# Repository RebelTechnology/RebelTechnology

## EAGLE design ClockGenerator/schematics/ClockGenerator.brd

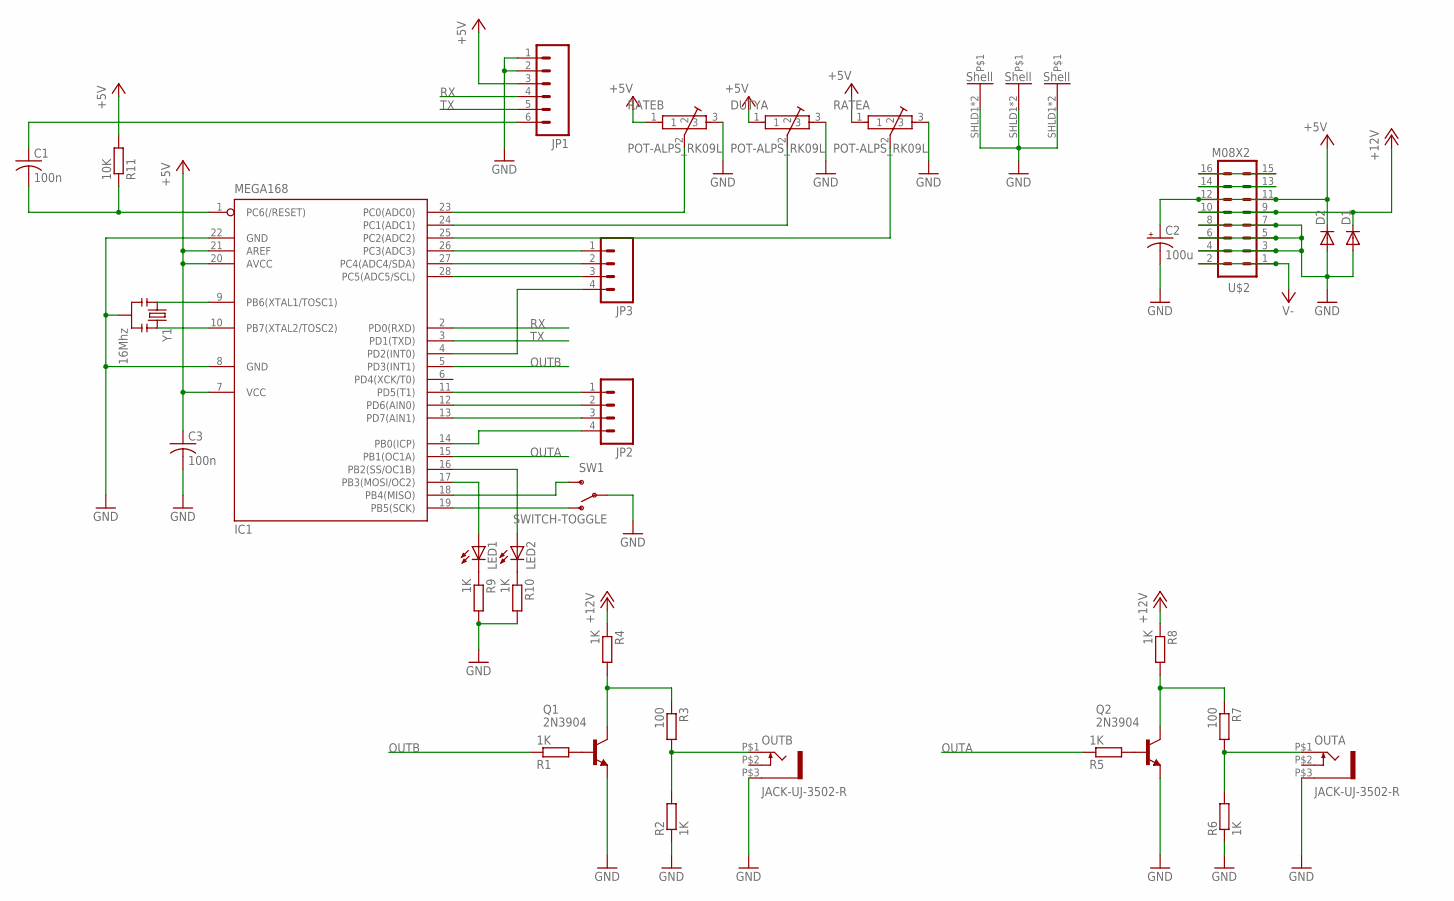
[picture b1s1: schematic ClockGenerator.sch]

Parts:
C1, C3: 100n; C050-024X044
C2: 100u; CPOL-RADIAL-100UF-25V
D1, D2: DIODEPTH; DIODE-1N4001
DUTYA: POT-ALPS_RK09L; POT-ALPS_RK09L1120
IC1: MEGA168; DIL28-3
JP1: M06SIP; 1X06
JP2, JP3: M04PTH; 1X04
LED1, LED2: LED3MM
OUTA: JACK-UJ-3502-R; UJ-3502-R
OUTB: JACK-UJ-3502-R; UJ-3502-R
Q1, Q2: 2N3904; TO92
R1, R2, R4, R5, R6, R8, R9, R10: 1K; 0204/7
R3, R7: 100; 0204/7
R11: 10K; 0204/7
RATEA: POT-ALPS_RK09L; POT-ALPS_RK09L1120
RATEB: POT-ALPS_RK09L; POT-ALPS_RK09L1120
SW1: SWITCH-TOGGLE; SWITCH-SPDT-SALECOM-T8020
U$2: M08X2; 2X8
Y1: 16Mhz; RESONATOR-PTH

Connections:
+5V: C2.1 (+), C3.1, D2.C, DUTYA.1, IC1.7 (VCC), IC1.20 (AVCC), IC1.21 (AREF), JP1.3, R11.2, RATEA.1, RATEB.1, U$2.11, U$2.12
+12V: D1.C, R4.1, R8.1, U$2.9, U$2.10
GND: C2.2 (-), C3.2, D1.A, D2.A, DUTYA.3, DUTYA.SHLD1, DUTYA.SHLD2, IC1.8 (GND), IC1.22 (GND), JP1.1, JP1.2, OUTA.P$3 (SLEEVE), OUTB.P$3 (SLEEVE), Q1.3 (E), Q2.3 (E), R2.1, R6.1, R9.2, R10.2, RATEA.3, RATEA.SHLD1, RATEA.SHLD2, RATEB.3, RATEB.SHLD1, RATEB.SHLD2, SW1.2, U$2.3, U$2.4, U$2.5, U$2.6, U$2.7, U$2.8, Y1.2
unnamed: IC1.23 (PC0(ADC0)), RATEB.2
unnamed: DUTYA.2, IC1.24 (PC1(ADC1))
unnamed: IC1.25 (PC2(ADC2)), RATEA.2
unnamed: IC1.19 (PB5(SCK)), SW1.1 (O)
unnamed: IC1.11 (PD5(T1)), JP2.1
unnamed: IC1.16 (PB2(SS/OC1B)), LED2.A
unnamed: IC1.9 (PB6(XTAL1/TOSC1)), Y1.1
unnamed: IC1.10 (PB7(XTAL2/TOSC2)), Y1.3
unnamed: IC1.17 (PB3(MOSI/OC2)), LED1.A
unnamed: IC1.4 (PD2(INT0)), JP3.4
unnamed: IC1.28 (PC5(ADC5/SCL)), JP3.3
unnamed: IC1.27 (PC4(ADC4/SDA)), JP3.2
unnamed: OUTB.P$1 (TIP), R2.2, R3.2
unnamed: Q1.1 (C), R3.1, R4.2
unnamed: IC1.26 (PC3(ADC3)), JP3.1
unnamed: IC1.12 (PD6(AIN0)), JP2.2
unnamed: IC1.13 (PD7(AIN1)), JP2.3
unnamed: U$2.13, U$2.14
unnamed: IC1.14 (PB0(ICP)), JP2.4
unnamed: IC1.18 (PB4(MISO)), SW1.3 (S)
unnamed: Q1.2 (B), R1.2
unnamed: Q2.2 (B), R5.2
unnamed: OUTA.P$1 (TIP), R6.2, R7.2
unnamed: Q2.1 (C), R7.1, R8.2
unnamed: LED1.K (C), R9.1
unnamed: C1.1, JP1.6
unnamed: LED2.K (C), R10.1
unnamed: C1.2, IC1.1 (PC6(/RESET)), R11.1
OUTA: IC1.15 (PB1(OC1A)), R5.1
OUTB: IC1.5 (PD3(INT1)), R1.1
PWR_BUS: U$2.15, U$2.16
RX: IC1.2 (PD0(RXD)), JP1.4
TX: IC1.3 (PD1(TXD)), JP1.5
V-: U$2.1, U$2.2

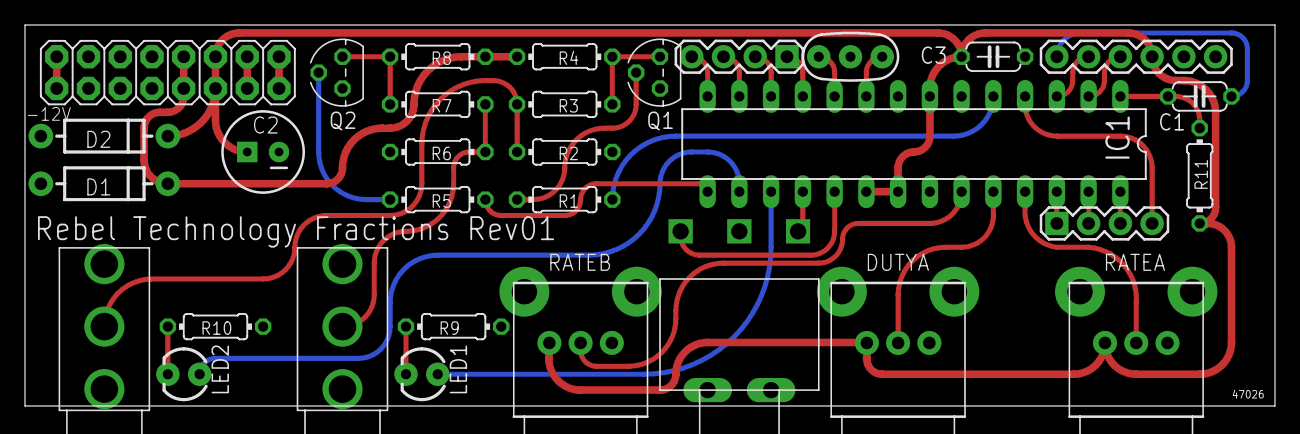
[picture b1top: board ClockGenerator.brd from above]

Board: 2 copper layers, 100.0 x 30.5 mm, 32 parts (0 on the bottom side), 37 nets.

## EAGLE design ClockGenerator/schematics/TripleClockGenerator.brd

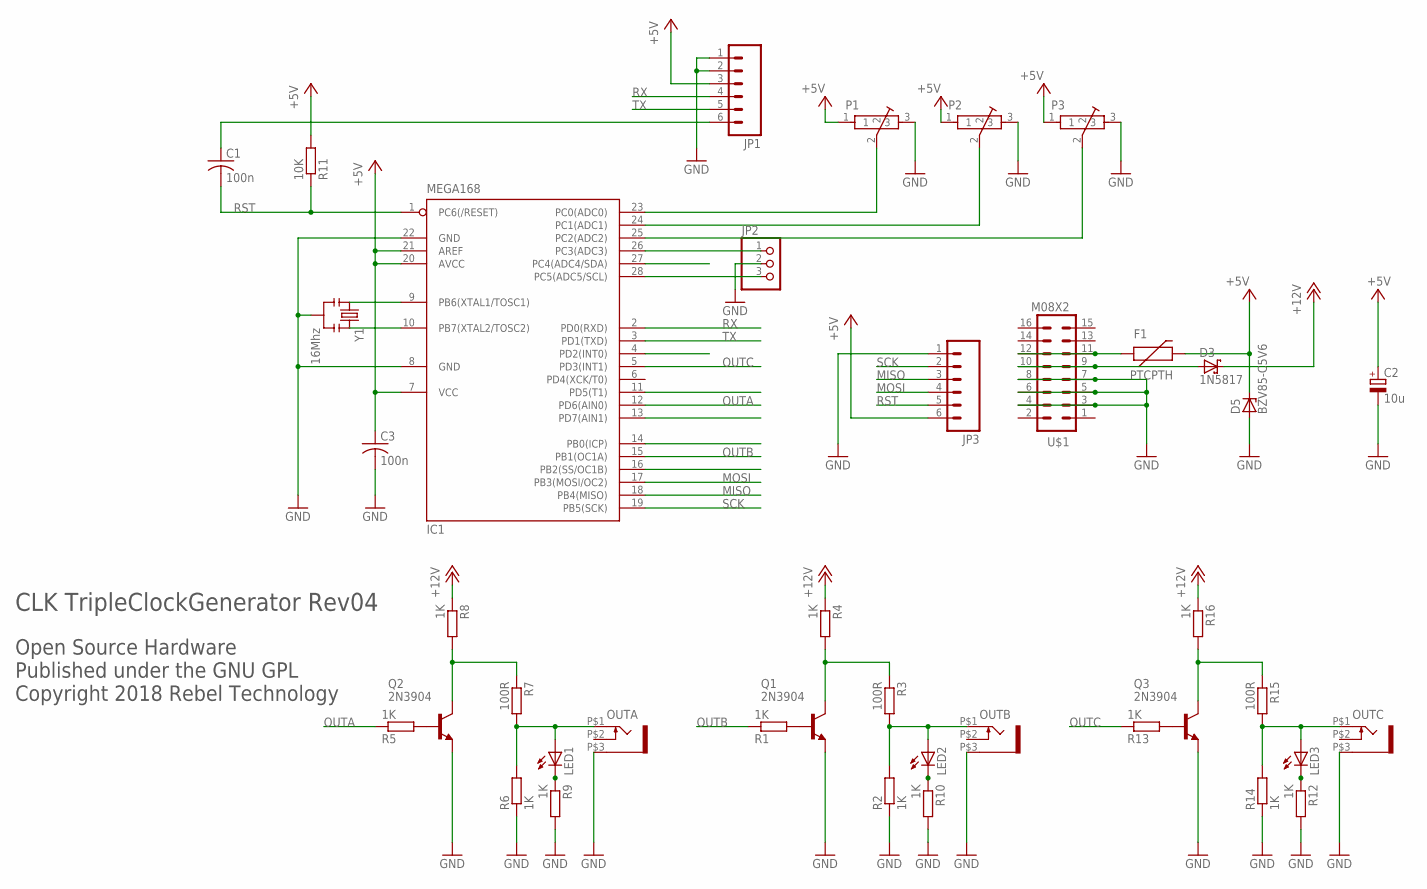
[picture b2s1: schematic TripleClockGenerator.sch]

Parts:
C1, C3: 100n; C050-024X044
C2: 10u; E5-6
D3: 1N5817; DO41-7.6
D5: BZV85-C5V6; DO34Z7
F1: PTCPTH; PTC
IC1: MEGA168; DIL28-3
JP1, JP3: M06SIP; 1X06
JP2: PINHD-1X3; 1X03
LED1, LED2, LED3: LED3MM
OUTA: JACK-UJ-3502-RSLOT; UJ-3502-R-SLOT
OUTB: JACK-UJ-3502-RSLOT; UJ-3502-R-SLOT
OUTC: JACK-UJ-3502-RSLOT; UJ-3502-R-SLOT
P1, P2, P3: POT-BOURNS-PTD901
Q1, Q2, Q3: 2N3904; TO92
R1, R2, R4, R5, R6, R8, R9, R10, R12, R13, R14, R16: 1K; 0204/7
R3, R7, R15: 100R; 0204/7
R11: 10K; 0204/7
U$1: M08X2; 2X8
Y1: 16Mhz; RESONATOR-PTH

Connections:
+5V: C2.+, C3.1, D5.C, F1.P$2 (2), IC1.7 (VCC), IC1.20 (AVCC), IC1.21 (AREF), JP1.3, JP3.6, P1.1, P2.1, P3.1, R11.2
+12V: D3.C, R4.1, R8.1, R16.1
ADC0: IC1.23 (PC0(ADC0)), P1.2
ADC1: IC1.24 (PC1(ADC1)), P2.2
ADC2: IC1.25 (PC2(ADC2)), P3.2
GND: C2.-, C3.2, D5.A, IC1.8 (GND), IC1.22 (GND), JP1.1, JP1.2, JP2.2, JP3.1, OUTA.P$3 (SLEEVE), OUTB.P$3 (SLEEVE), OUTC.P$3 (SLEEVE), P1.3, P2.3, P3.3, Q1.3 (E), Q2.3 (E), Q3.3 (E), R2.1, R6.1, R9.2, R10.2, R12.2, R14.1, U$1.3, U$1.4, U$1.5, U$1.6, U$1.7, U$1.8, Y1.2
MISO: IC1.18 (PB4(MISO)), JP3.3
MOSI: IC1.17 (PB3(MOSI/OC2)), JP3.4
unnamed: LED3.K (C), R12.1
unnamed: IC1.9 (PB6(XTAL1/TOSC1)), Y1.1
unnamed: IC1.10 (PB7(XTAL2/TOSC2)), Y1.3
unnamed: IC1.28 (PC5(ADC5/SCL)), JP2.3
unnamed: LED2.A, OUTB.P$1 (TIP), R2.2, R3.2
unnamed: Q1.1 (C), R3.1, R4.2
unnamed: IC1.26 (PC3(ADC3)), JP2.1
unnamed: Q1.2 (B), R1.2
unnamed: Q3.2 (B), R13.2
unnamed: LED3.A, OUTC.P$1 (TIP), R14.2, R15.2
unnamed: Q3.1 (C), R15.1, R16.2
unnamed: Q2.2 (B), R5.2
unnamed: LED1.A, OUTA.P$1 (TIP), R6.2, R7.2
unnamed: Q2.1 (C), R7.1, R8.2
unnamed: LED1.K (C), R9.1
unnamed: C1.1, JP1.6
unnamed: LED2.K (C), R10.1
unnamed: F1.P$1 (1), U$1.11, U$1.12
unnamed: D3.A, U$1.9, U$1.10
OUTA: IC1.12 (PD6(AIN0)), R5.1
OUTB: IC1.15 (PB1(OC1A)), R1.1
OUTC: IC1.5 (PD3(INT1)), R13.1
RST: C1.2, IC1.1 (PC6(/RESET)), JP3.5, R11.1
RX: IC1.2 (PD0(RXD)), JP1.4
SCK: IC1.19 (PB5(SCK)), JP3.2
TX: IC1.3 (PD1(TXD)), JP1.5

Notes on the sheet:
Open Source Hardware Published under the GNU GPL Copyright 2018 Rebel Technology
CLK TripleClockGenerator Rev04

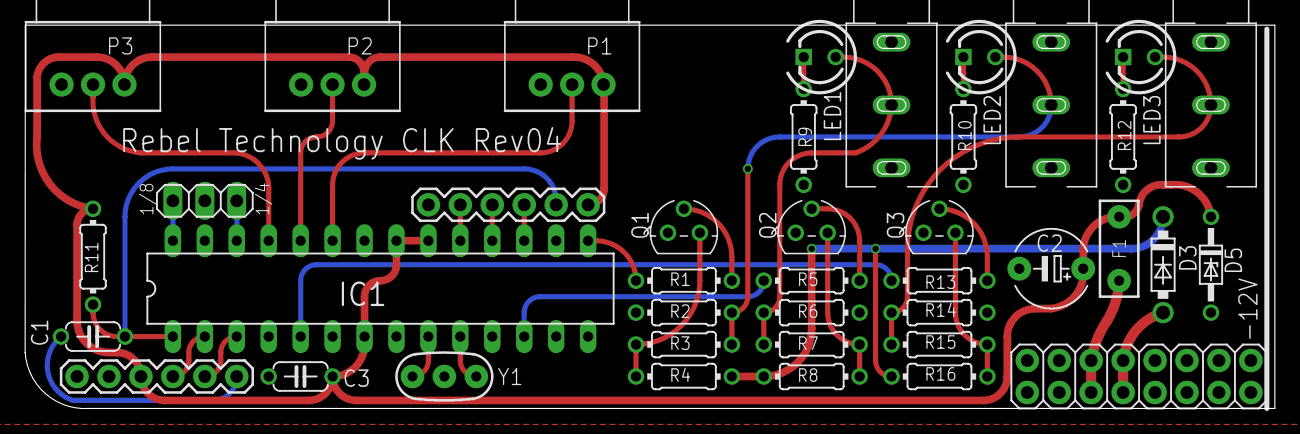
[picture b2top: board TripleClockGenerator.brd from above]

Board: 2 copper layers, 99.4 x 30.5 mm, 40 parts (0 on the bottom side), 34 nets.

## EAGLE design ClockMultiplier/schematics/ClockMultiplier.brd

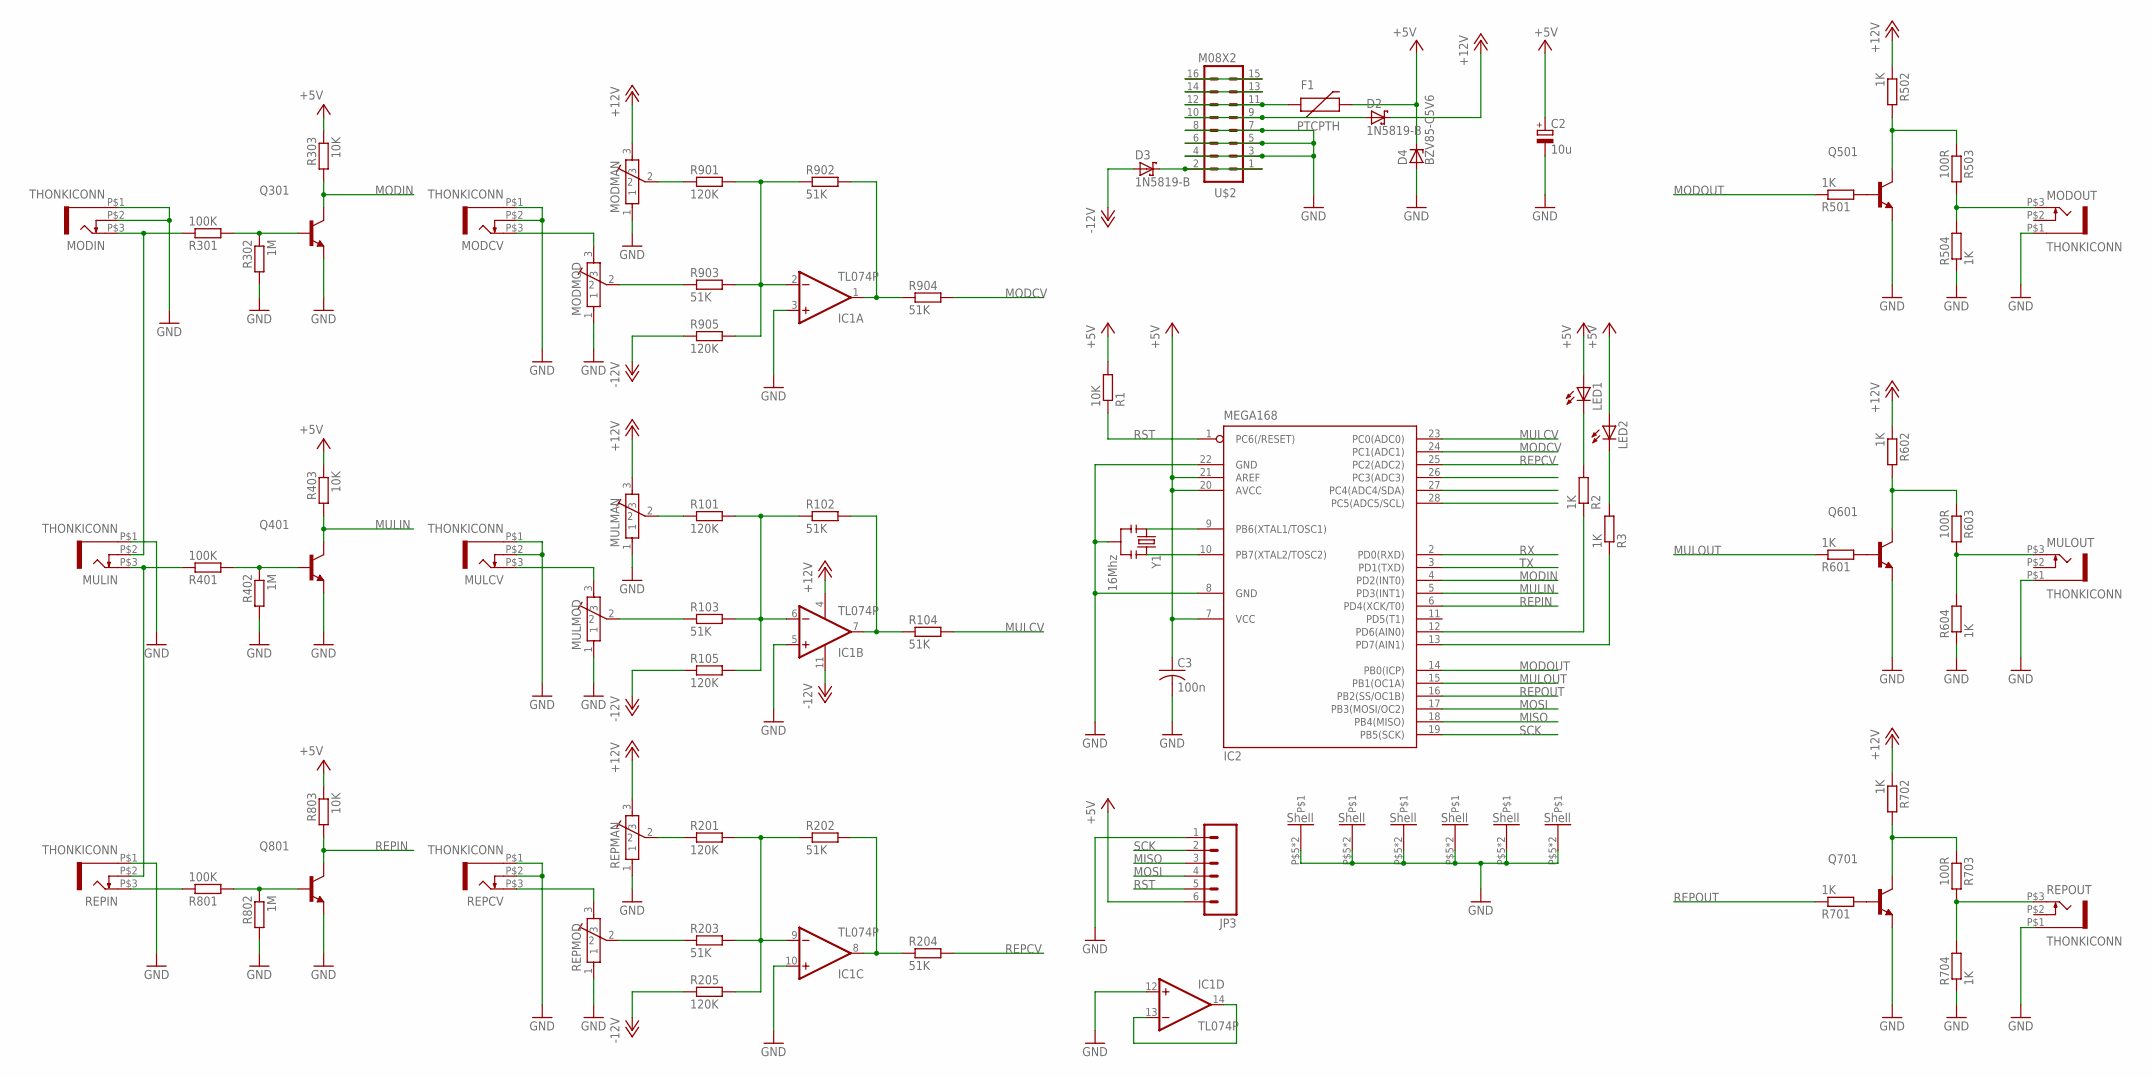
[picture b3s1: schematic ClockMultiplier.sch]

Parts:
C2: 10u; E5-6
C3: 100n; C050-024X044
D2, D3: 1N5819-B; DO41-7.6
D4: BZV85-C5V6; DO34Z7
F1: PTCPTH; PTC
IC1: TL074P; DIL14
IC2: MEGA168; DIL28-3
JP3: M06SIP; 1X06
LED1, LED2: LED3MM
MODCV: THONKICONN
MODIN: THONKICONN
MODMAN: POT-ALPS-RK09L1140
MODMOD: POT-ALPS-RK09L1140
MODOUT: THONKICONN
MULCV: THONKICONN
MULIN: THONKICONN
MULMAN: POT-ALPS-RK09L1140
MULMOD: POT-ALPS-RK09L1140
MULOUT: THONKICONN
Q301, Q401, Q501, Q601, Q701, Q801: 2N3904-NPN-TO92-EBC; TO92-EBC
R1, R303, R403, R803: 10K; 0204/7
R2, R3, R501, R502, R504, R601, R602, R604, R701, R702, R704: 1K; 0204/7
R101, R105, R201, R205, R901, R905: 120K; 0204/7
R102, R103, R104, R202, R203, R204, R902, R903, R904: 51K; 0204/7
R301, R401, R801: 100K; 0204/7
R302, R402, R802: 1M; 0204/7
R503, R603, R703: 100R; 0204/7
REPCV: THONKICONN
REPIN: THONKICONN
REPMAN: POT-ALPS-RK09L1140
REPMOD: POT-ALPS-RK09L1140
REPOUT: THONKICONN
U$2: M08X2; 2X8
Y1: 16Mhz; RESONATOR-PTH

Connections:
+5V: C2.+, C3.1, D4.C, F1.P$2 (2), IC2.7 (VCC), IC2.20 (AVCC), IC2.21 (AREF), JP3.6, LED1.A, LED2.A, R1.2, R303.1, R403.1, R803.1
+12V: D2.C, IC1.4 (V+), MODMAN.3, MULMAN.3, R502.1, R602.1, R702.1, REPMAN.3
-12V: D3.A, IC1.11 (V-), R105.1, R205.1, R905.1
DURSW: MODIN.P$3 (3), MULIN.P$2 (4), R301.1
GND: C2.-, C3.2, D4.A, IC1.3 (+IN), IC1.5 (+IN), IC1.10 (+IN), IC1.12 (+IN), IC2.8 (GND), IC2.22 (GND), JP3.1, MODCV.P$1 (5), MODCV.P$2 (4), MODIN.P$1 (5), MODIN.P$2 (4), MODMAN.1, MODMAN.P$5, MODMAN.P$6, MODMOD.1, MODMOD.P$5, MODMOD.P$6, MODOUT.P$1 (5), MULCV.P$1 (5), MULCV.P$2 (4), MULIN.P$1 (5), MULMAN.1, MULMAN.P$5, MULMAN.P$6, MULMOD.1, MULMOD.P$5, MULMOD.P$6, MULOUT.P$1 (5), Q301.E, Q401.E, Q501.E, Q601.E, Q701.E, Q801.E, R302.2, R402.2, R504.1, R604.1, R704.1, R802.2, REPCV.P$1 (5), REPCV.P$2 (4), REPIN.P$1 (5), REPMAN.1, REPMAN.P$5, REPMAN.P$6, REPMOD.1, REPMOD.P$5, REPMOD.P$6, REPOUT.P$1 (5), U$2.3, U$2.4, U$2.5, U$2.6, U$2.7, U$2.8, Y1.2
MISO: IC2.18 (PB4(MISO)), JP3.3
MODCV: IC2.24 (PC1(ADC1)), R904.2
MODIN: IC2.4 (PD2(INT0)), Q301.C, R303.2
MODOUT: IC2.14 (PB0(ICP)), R501.1
MOSI: IC2.17 (PB3(MOSI/OC2)), JP3.4
MULCV: IC2.23 (PC0(ADC0)), R104.2
MULIN: IC2.5 (PD3(INT1)), Q401.C, R403.2
MULOUT: IC2.15 (PB1(OC1A)), R601.1
unnamed: MULCV.P$3 (3), MULMOD.3
unnamed: IC1.6 (-IN), R101.2, R102.1, R103.2, R105.2
unnamed: MULMAN.2, R101.1
unnamed: IC1.7 (OUT), R102.2, R104.1
unnamed: MULMOD.2, R103.1
unnamed: D3.C, U$2.1, U$2.2
unnamed: IC1.9 (-IN), R201.2, R202.1, R203.2, R205.2
unnamed: R201.1, REPMAN.2
unnamed: IC1.8 (OUT), R202.2, R204.1
unnamed: R203.1, REPMOD.2
unnamed: IC1.13 (-IN), IC1.14 (OUT)
unnamed: REPCV.P$3 (3), REPMOD.3
unnamed: IC1.2 (-IN), R901.2, R902.1, R903.2, R905.2
unnamed: MODMAN.2, R901.1
unnamed: IC1.1 (OUT), R902.2, R904.1
unnamed: MODMOD.2, R903.1
unnamed: IC2.9 (PB6(XTAL1/TOSC1)), Y1.1
unnamed: IC2.10 (PB7(XTAL2/TOSC2)), Y1.3
unnamed: MODCV.P$3 (3), MODMOD.3
unnamed: LED1.K (C), R2.2
unnamed: LED2.K (C), R3.2
unnamed: IC2.13 (PD7(AIN1)), R3.1
unnamed: Q601.B, R601.2
unnamed: Q301.B, R301.2, R302.1
unnamed: MODOUT.P$3 (3), R503.2, R504.2
unnamed: IC2.12 (PD6(AIN0)), R2.1
unnamed: MULOUT.P$3 (3), R603.2, R604.2
unnamed: Q401.B, R401.2, R402.1
unnamed: Q601.C, R602.2, R603.1
unnamed: Q501.B, R501.2
unnamed: Q701.B, R701.2
unnamed: R703.2, R704.2, REPOUT.P$3 (3)
unnamed: MULIN.P$3 (3), R401.1, REPIN.P$2 (4)
unnamed: Q501.C, R502.2, R503.1
unnamed: Q701.C, R702.2, R703.1
unnamed: Q801.B, R801.2, R802.1
unnamed: R801.1, REPIN.P$3 (3)
unnamed: U$2.13, U$2.14
unnamed: F1.P$1 (1), U$2.11, U$2.12
unnamed: D2.A, U$2.9, U$2.10
PWR_BUS: U$2.15, U$2.16
REPCV: IC2.25 (PC2(ADC2)), R204.2
REPIN: IC2.6 (PD4(XCK/T0)), Q801.C, R803.2
REPOUT: IC2.16 (PB2(SS/OC1B)), R701.1
RST: IC2.1 (PC6(/RESET)), JP3.5, R1.1
RX: IC2.2 (PD0(RXD))
SCK: IC2.19 (PB5(SCK)), JP3.2
TX: IC2.3 (PD1(TXD))

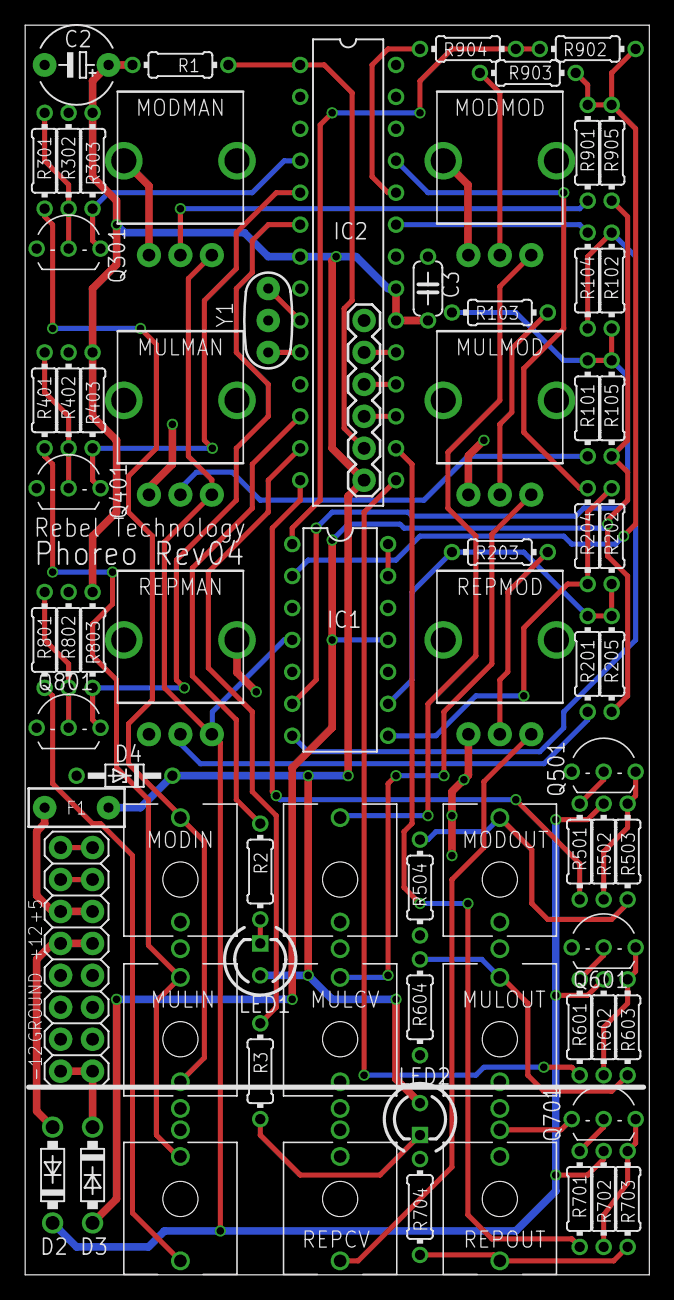
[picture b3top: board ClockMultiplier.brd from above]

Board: 2 copper layers, 49.6 x 99.4 mm, 73 parts (0 on the bottom side), 59 nets.

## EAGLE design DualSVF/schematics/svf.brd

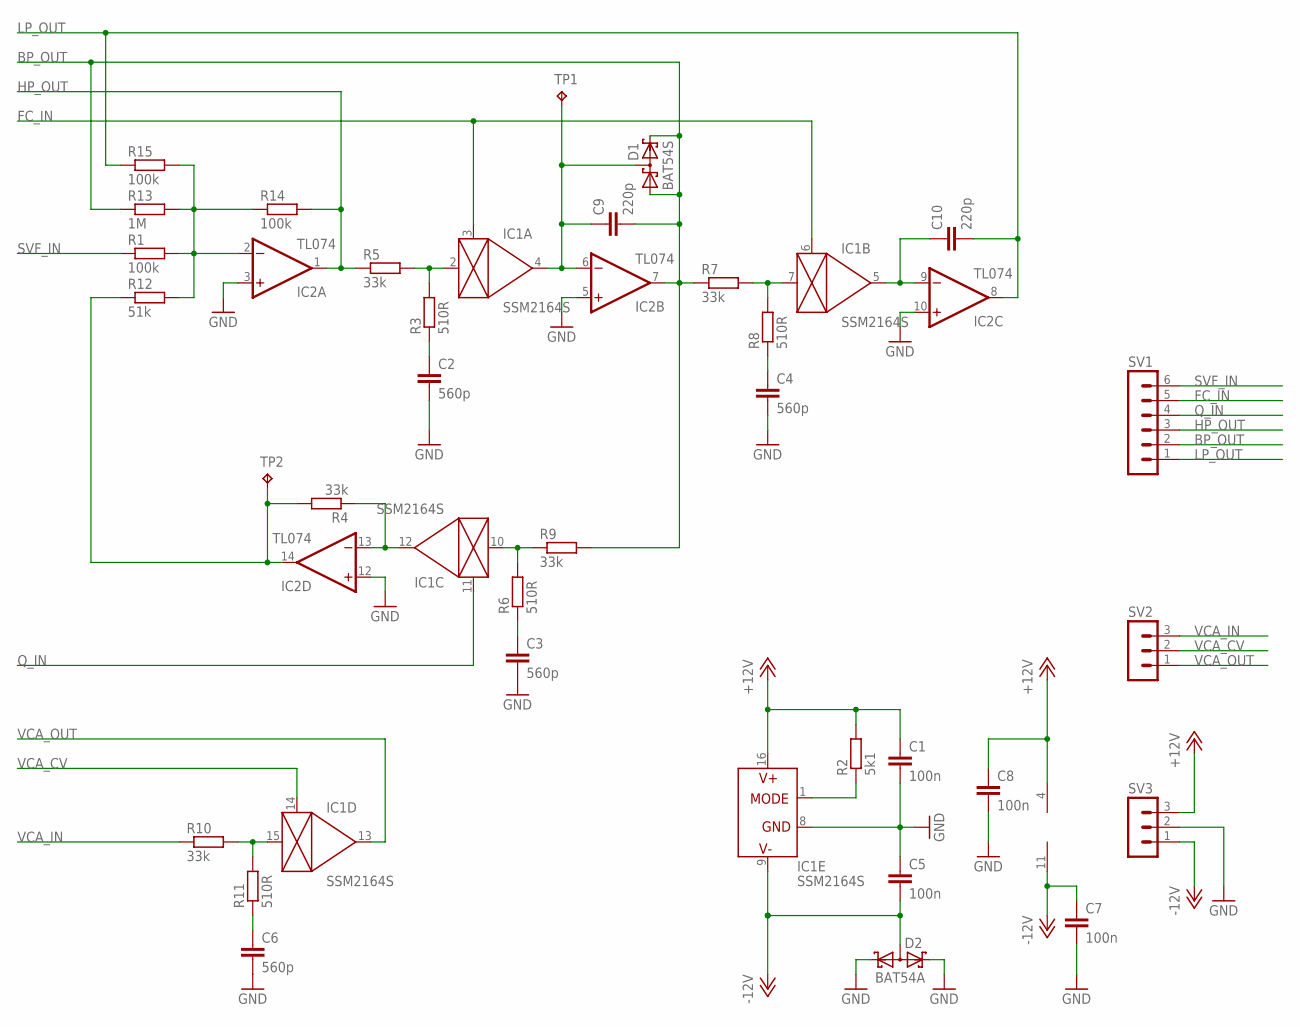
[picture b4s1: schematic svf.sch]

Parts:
C1, C5, C7, C8: 100n; C0603
C2, C3, C4, C6: 560p; C0603
C9, C10: 220p; C0603
D1: BAT54S; SOT23
D2: BAT54A; SOT23
IC1: SSM2164S; SOIC16N
IC2: TL074; SO14
R1, R14, R15: 100k; 0603
R2: 5k1; 0603
R3, R6, R8, R11: 510R; 0603
R4, R5, R7, R9, R10: 33k; 0603
R12: 51k; 0603
R13: 1M; 0603
SV1: MA06-1
SV2, SV3: MA03-1
TP1, TP2: TPPAD1-13; P1-13

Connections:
+12V: C1.1, C8.1, IC1.16 (V+), IC2.4 (V+), R2.2, SV3.3
-12V: C5.2, C7.1, D2.3 (AA), IC1.9 (V-), IC2.11 (V-), SV3.1
BP_OUT: C9.2, D1.1 (A1), D1.2 (C2), IC2.7 (OUT), R7.1, R9.2, R13.1, SV1.2
FB_IN: IC2.14 (OUT), R4.2, R12.1, TP2.TP
FC_IN: IC1.3 (CTRL), IC1.6 (CTRL), SV1.5
GND: C1.2, C2.2, C3.2, C4.2, C5.1, C6.2, C7.2, C8.2, D2.1 (K1), D2.2 (K2), IC1.8 (GND), IC2.3 (+IN), IC2.5 (+IN), IC2.10 (+IN), IC2.12 (+IN), SV3.2
HP_OUT: IC2.1 (OUT), R5.1, R14.2, SV1.3
LP_OUT: C10.2, IC2.8 (OUT), R15.1, SV1.1
unnamed: IC1.1 (MODE), R2.1
unnamed: IC1.7 (IN), R7.2, R8.2
unnamed: C10.1, IC1.5 (OUT), IC2.9 (-IN)
unnamed: C4.1, R8.1
unnamed: IC1.12 (OUT), IC2.13 (-IN), R4.1
unnamed: IC2.2 (-IN), R1.2, R12.2, R13.2, R14.1, R15.2
unnamed: C6.1, R11.1
unnamed: C9.1, D1.3 (C1A2), IC1.4 (OUT), IC2.6 (-IN), TP1.TP
unnamed: IC1.10 (IN), R6.2, R9.1
unnamed: IC1.15 (IN), R10.2, R11.2
unnamed: C3.1, R6.1
unnamed: IC1.2 (IN), R3.2, R5.2
unnamed: C2.1, R3.1
Q_IN: IC1.11 (CTRL), SV1.4
SVF_IN: R1.1, SV1.6
VCA_CV: IC1.14 (CTRL), SV2.2
VCA_IN: R10.1, SV2.3
VCA_OUT: IC1.13 (OUT), SV2.1

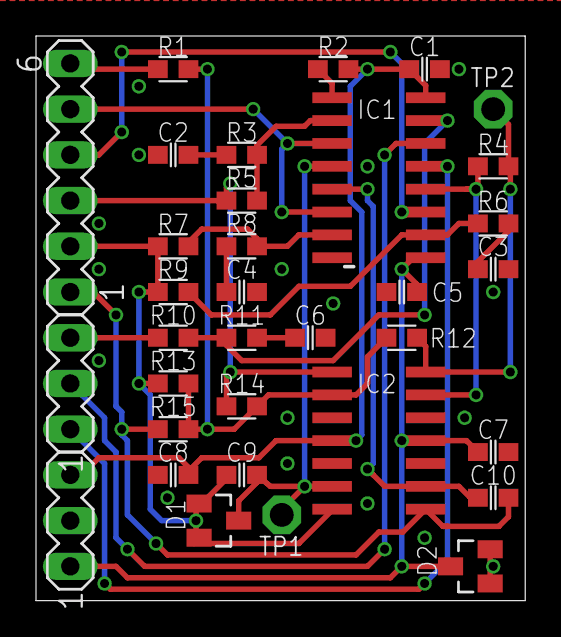
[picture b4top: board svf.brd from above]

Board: 2 copper layers, 27.2 x 31.4 mm, 34 parts (0 on the bottom side), 26 nets.

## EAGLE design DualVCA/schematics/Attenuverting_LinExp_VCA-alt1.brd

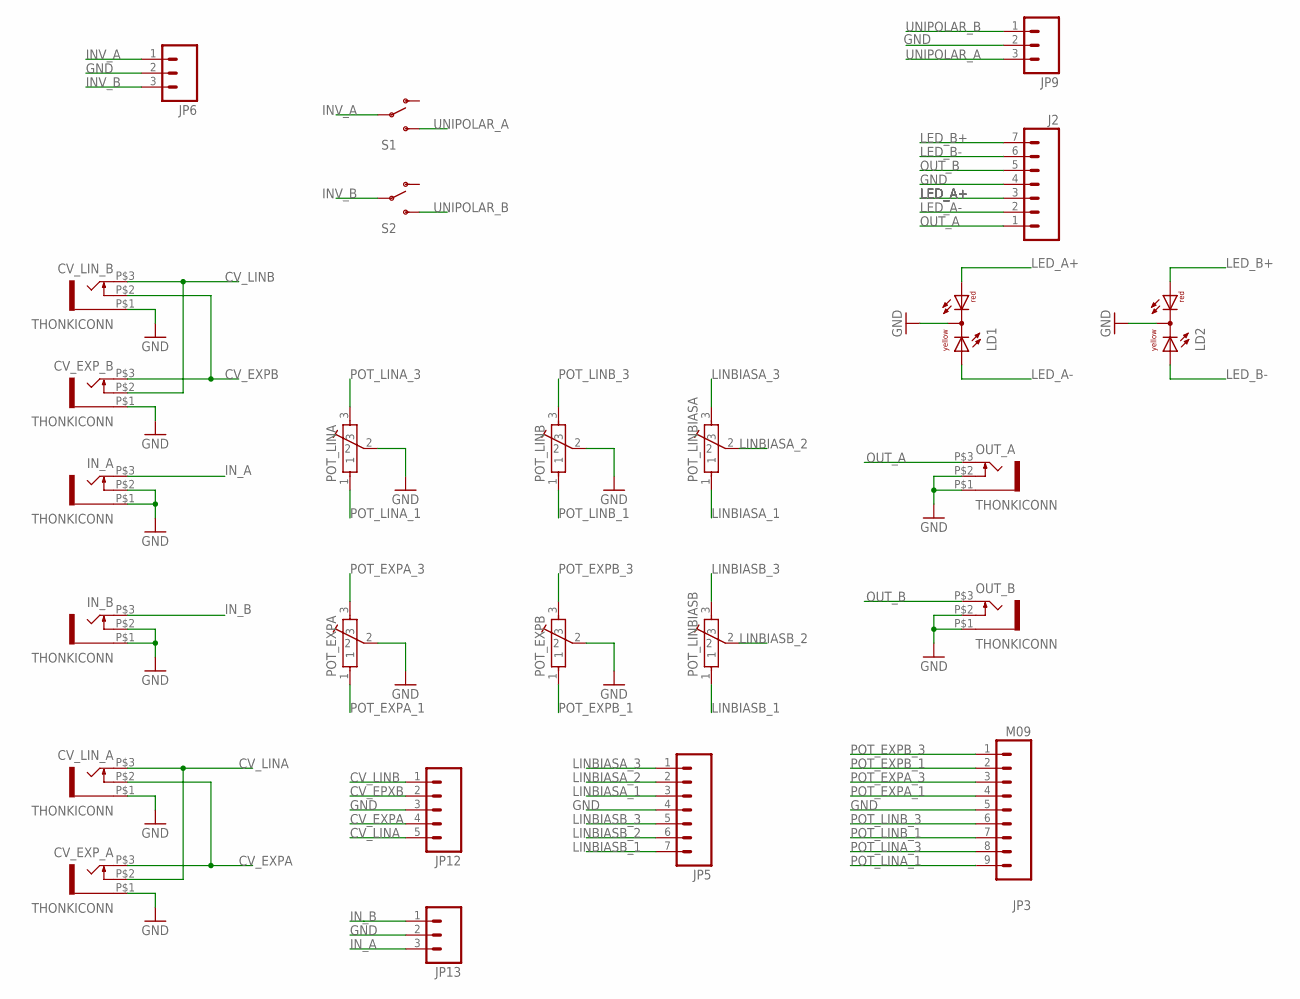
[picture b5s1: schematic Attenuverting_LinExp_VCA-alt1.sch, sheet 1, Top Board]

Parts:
CV_EXP_A: THONKICONN
CV_EXP_B: THONKICONN
CV_LIN_A: THONKICONN
CV_LIN_B: THONKICONN
IN_A: THONKICONN
IN_B: THONKICONN
J2: M07; 1X07
JP3: M09; 1X09
JP5: M07; 1X07
JP6, JP9, JP13: M03PTH; 1X03
JP12: M05PTH; 1X05
LD1, LD2: DUOLED-RY-C; DUOLED-C-5MM
OUT_A: THONKICONN
OUT_B: THONKICONN
POT_EXPA: POT-ALPS-RK09L1140
POT_EXPB: POT-ALPS-RK09L1140
POT_LINA: POT-ALPS-RK09L1140
POT_LINB: POT-ALPS-RK09L1140
POT_LINBIASA: POT-ALPS-RK09L1140
POT_LINBIASB: POT-ALPS-RK09L1140
S1, S2: SWITCH-SPST; SWITCH-SPDT-SALECOM-T8014

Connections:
CV_EPXB: JP12.2
CV_EXPA: CV_EXP_A.P$3 (3), CV_LIN_A.P$2 (4), JP12.4; also elsewhere on the board
CV_EXPB: CV_EXP_B.P$3 (3), CV_LIN_B.P$2 (4); also elsewhere on the board
CV_LINA: CV_EXP_A.P$2 (4), CV_LIN_A.P$3 (3), JP12.5; also elsewhere on the board
CV_LINB: CV_EXP_B.P$2 (4), CV_LIN_B.P$3 (3), JP12.1; also elsewhere on the board
GND: CV_EXP_A.P$1 (5), CV_EXP_B.P$1 (5), CV_LIN_A.P$1 (5), CV_LIN_B.P$1 (5), IN_A.P$1 (5), IN_A.P$2 (4), IN_B.P$1 (5), IN_B.P$2 (4), J2.4, JP3.5, JP5.4, JP6.2, JP9.2, JP12.3, JP13.2, LD1.C, LD2.C, OUT_A.P$1 (5), OUT_A.P$2 (4), OUT_B.P$1 (5), OUT_B.P$2 (4), POT_EXPA.2, POT_EXPB.2, POT_LINA.2, POT_LINB.2; also elsewhere on the board
INV_A: JP6.1, S1.2; also elsewhere on the board
INV_B: JP6.3, S2.2; also elsewhere on the board
IN_A: IN_A.P$3 (3), JP13.3; also elsewhere on the board
IN_B: IN_B.P$3 (3), JP13.1; also elsewhere on the board
LED_A+: J2.3, LD1.AR; also elsewhere on the board
LED_A-: J2.2, LD1.AX (AY); also elsewhere on the board
LED_B+: J2.7, LD2.AR; also elsewhere on the board
LED_B-: J2.6, LD2.AX (AY); also elsewhere on the board
LINBIASA_1: JP5.3, POT_LINBIASA.1; also elsewhere on the board
LINBIASA_2: JP5.2, POT_LINBIASA.2; also elsewhere on the board
LINBIASA_3: JP5.1, POT_LINBIASA.3; also elsewhere on the board
LINBIASB_1: JP5.7, POT_LINBIASB.1; also elsewhere on the board
LINBIASB_2: JP5.6, POT_LINBIASB.2; also elsewhere on the board
LINBIASB_3: JP5.5, POT_LINBIASB.3; also elsewhere on the board
OUT_A: J2.1, OUT_A.P$3 (3); also elsewhere on the board
OUT_B: J2.5, OUT_B.P$3 (3); also elsewhere on the board
POT_EXPA_1: JP3.4, POT_EXPA.1; also elsewhere on the board
POT_EXPA_3: JP3.3, POT_EXPA.3; also elsewhere on the board
POT_EXPB_1: JP3.2, POT_EXPB.1; also elsewhere on the board
POT_EXPB_3: JP3.1, POT_EXPB.3; also elsewhere on the board
POT_LINA_1: JP3.9, POT_LINA.1; also elsewhere on the board
POT_LINA_3: JP3.8, POT_LINA.3; also elsewhere on the board
POT_LINB_1: JP3.7, POT_LINB.1; also elsewhere on the board
POT_LINB_3: JP3.6, POT_LINB.3; also elsewhere on the board
UNIPOLAR_A: JP9.3, S1.3 (S); also elsewhere on the board
UNIPOLAR_B: JP9.1, S2.3 (S); also elsewhere on the board

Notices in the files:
parts and their libraries:
SparkFun: Licensing: CC v3.0 Share-Alike You are welcome to use this library for commercial purposes.
SparkFun-Aesthetics: Licensing: Creative Commons ShareAlike 4.0 International - https://creativecommons.org/licenses/by-sa/4.0
